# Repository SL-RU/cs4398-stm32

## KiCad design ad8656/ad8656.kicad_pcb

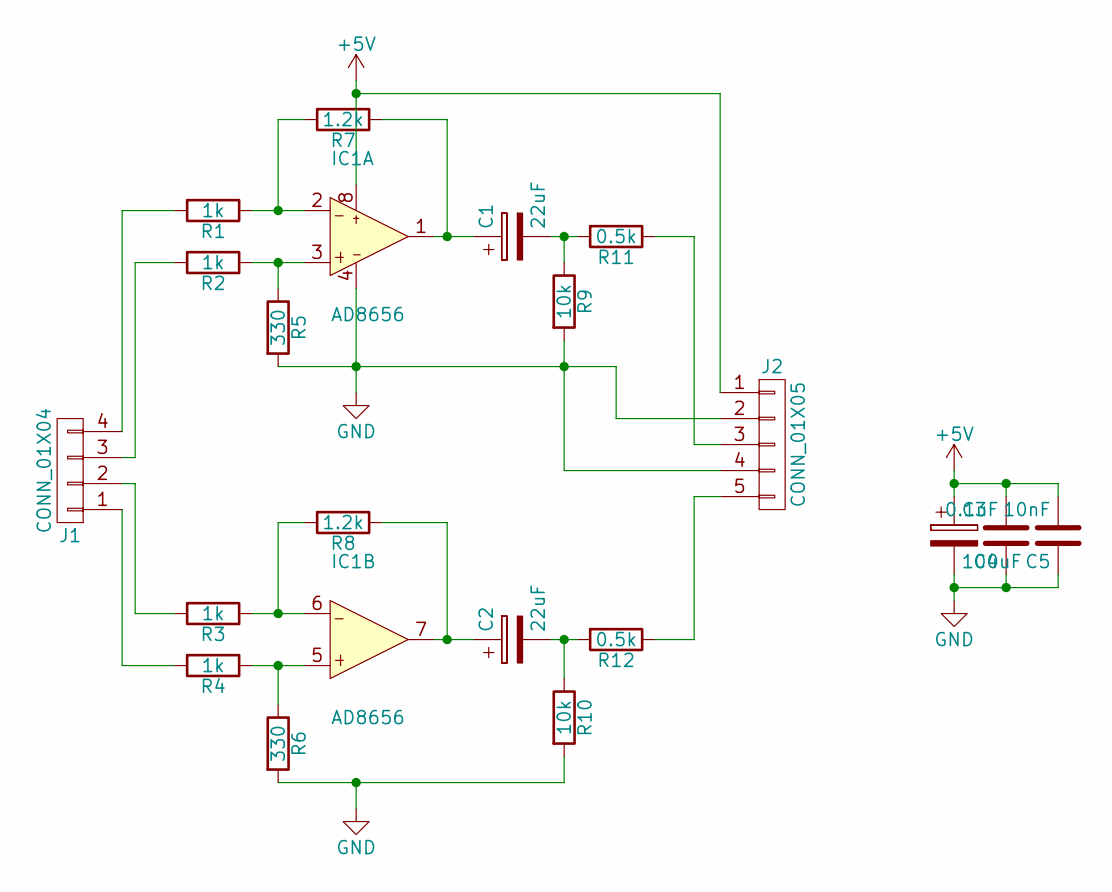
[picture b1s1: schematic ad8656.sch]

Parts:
C1, C2: 22uF; CP_Radial_D5.0mm_P2.50mm
C3: 100uF; CP_Radial_D5.0mm_P2.50mm
C4: 0.1uF; C_0402
C5: 10nF; C_0805_HandSoldering
IC1: AD8656; SOIC-8_3.9x4.9mm_Pitch1.27mm; Farnell 1858055
J1: CONN_01X04; Pin_Header_Straight_1x04_Pitch2.54mm
J2: CONN_01X05; Pin_Header_Straight_1x05_Pitch2.54mm
R1, R2, R3, R4: 1k; R_0603_HandSoldering
R5, R6: 330; R_0603_HandSoldering
R7, R8: 1.2k; R_0603_HandSoldering
R9, R10: 10k; R_0603_HandSoldering
R11, R12: 0.5k; R_0603_HandSoldering

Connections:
+5V: C3.1, C4.2, C5.2, IC1.8 (V+), J2.1
GND: C3.2, C4.1, C5.1, IC1.4 (V-), J2.2, J2.4, R5.2, R6.2, R9.2, R10.2
unnamed: C1.1, IC1.1 (OUT), R7.1
unnamed: C1.2, R9.1, R11.2
unnamed: C2.1, IC1.7 (OUT), R8.1
unnamed: C2.2, R10.1, R12.2
unnamed: IC1.2 (-IN), R1.1, R7.2
unnamed: IC1.3 (+IN), R2.1, R5.1
unnamed: IC1.5 (+IN), R4.1, R6.1
unnamed: IC1.6 (-IN), R3.1, R8.2
unnamed: J1.1, R4.2
unnamed: J1.2, R3.2
unnamed: J1.3, R2.2
unnamed: J1.4, R1.2
unnamed: J2.3, R11.1
unnamed: J2.5, R12.1

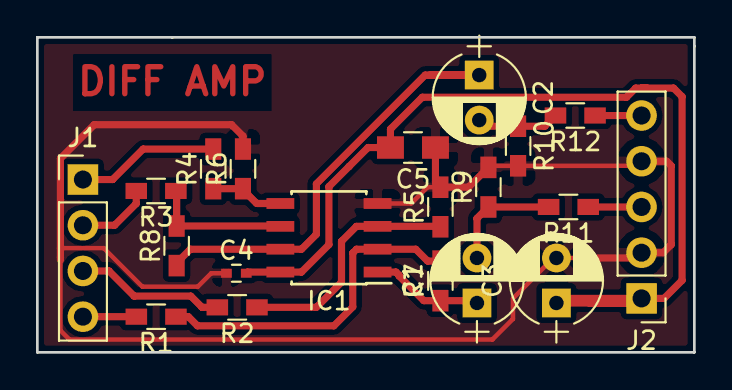
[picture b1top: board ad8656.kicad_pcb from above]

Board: 2 copper layers, 36.5 x 17.5 mm, 20 parts (0 on the bottom side), 16 nets.

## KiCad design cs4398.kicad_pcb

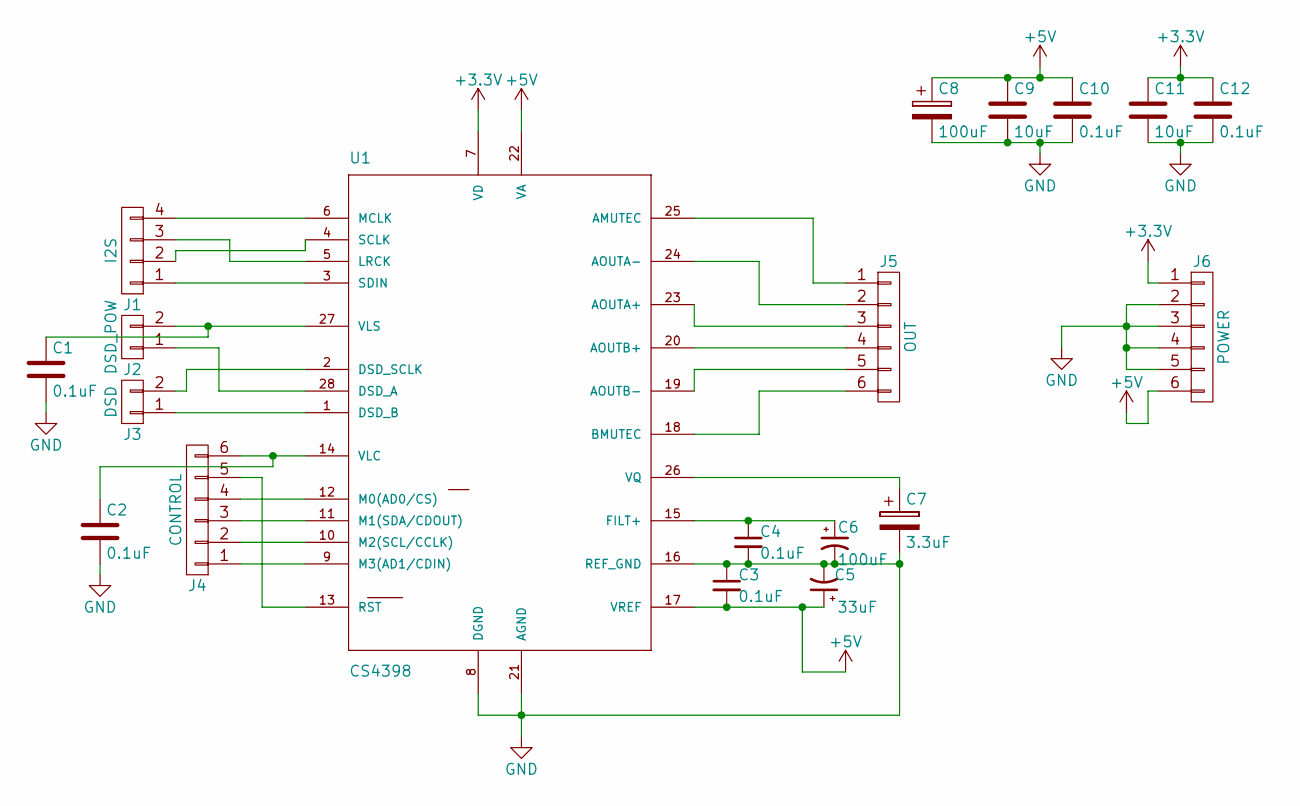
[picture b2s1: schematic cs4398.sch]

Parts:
C1, C2, C3, C4, C10, C12: 0.1uF; C_0402
C5: 33uF; CP_Radial_D4.0mm_P2.00mm
C6, C8: 100uF; CP_Radial_D4.0mm_P2.00mm
C7: 3.3uF; CP_Radial_D4.0mm_P2.00mm
C9, C11: 10uF; C_0805_HandSoldering
J1: I2S; Pin_Header_Straight_1x04_Pitch2.54mm
J2: DSD_POW; Pin_Header_Straight_1x02_Pitch2.54mm
J3: DSD; Pin_Header_Straight_1x02_Pitch2.54mm
J4: CONTROL; Pin_Header_Straight_1x06_Pitch2.54mm
J5: OUT; Pin_Header_Straight_1x06_Pitch2.54mm
J6: POWER; Pin_Header_Straight_1x06_Pitch2.54mm
U1: CS4398; TSSOP-28_4.4x9.7mm_Pitch0.65mm

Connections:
+3V3: C11.1, C12.1, J6.1, U1.7 (VD)
+5V: C3.2, C5.1, C8.1, C9.1, C10.1, J6.6, U1.17 (VREF), U1.22 (VA)
GND: C1.2, C2.2, C3.1, C4.2, C5.2, C6.2, C7.2, C8.2, C9.2, C10.2, C11.2, C12.2, J6.2, J6.3, J6.4, J6.5, U1.8 (DGND), U1.16 (REF_GND), U1.21 (AGND)
unnamed: C1.1, J2.2, U1.27 (VLS)
unnamed: C2.1, J4.6, U1.14 (VLC)
unnamed: C4.1, C6.1, U1.15 (FILT+)
unnamed: C7.1, U1.26 (VQ)
unnamed: J1.1, U1.3 (SDIN)
unnamed: J1.2, U1.4 (SCLK)
unnamed: J1.3, U1.5 (LRCK)
unnamed: J1.4, U1.6 (MCLK)
unnamed: J2.1, U1.28 (DSD_A)
unnamed: J3.1, U1.1 (DSD_B)
unnamed: J3.2, U1.2 (DSD_SCLK)
unnamed: J4.1, U1.9 (M3(AD1/CDIN))
unnamed: J4.2, U1.10 (M2(SCL/CCLK))
unnamed: J4.3, U1.11 (M1(SDA/CDOUT))
unnamed: J4.4, U1.12 (M0(AD0/CS))
unnamed: J4.5, U1.13 (RST)
unnamed: J5.1, U1.25 (AMUTEC)
unnamed: J5.2, U1.24 (AOUTA-)
unnamed: J5.3, U1.23 (AOUTA+)
unnamed: J5.4, U1.20 (AOUTB+)
unnamed: J5.5, U1.19 (AOUTB-)
unnamed: J5.6, U1.18 (BMUTEC)

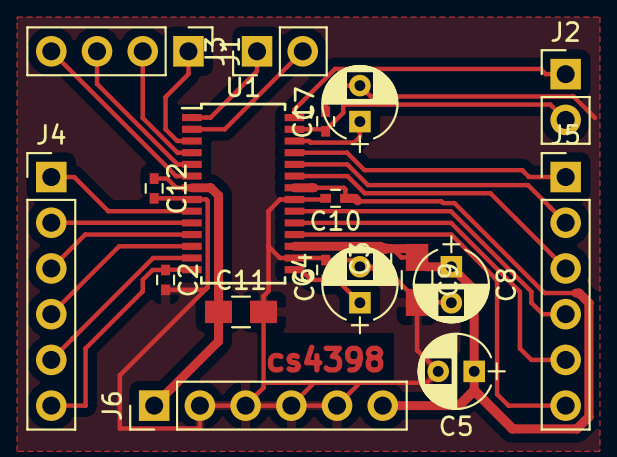
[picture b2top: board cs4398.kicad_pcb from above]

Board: 2 copper layers, 19 parts (0 on the bottom side), 25 nets.

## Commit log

2017-05-01 first
2017-05-01 amplifier
